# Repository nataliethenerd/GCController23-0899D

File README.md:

# Game Cube Controller 23-0899D reverse engineer

**ORDER WITH ENIG**

Thanks to the people who have supported me on Ko-Fi, you've made this possible! 

You can support me on Ko-Fi

## Scans

HD scans of the original board can be found [here](https://github.com/nataliethenerd/boardscans/tree/main/GCC-23-0899D)

**My socials**

• [Twitter](https://twitter.com/natalie_thenerd) 

• [Instagram](https://www.instagram.com/natalie.thenerd/) 

• [Modded Gameboy Club](https://moddedgameboy.club/) - a club dedicated to the modification of Game Boys, freely sharing resources

## License

Please do not remove my logo, website and name.

The CC BY-SA 4.0 (Creative Commons Attribution-ShareAlike 4.0 International) license allows you to:

1. **Share** - Copy and redistribute the material in any medium or format.
2. **Adapt** - Remix, transform, and build upon the material for any purpose, even commercially.

### Conditions:

- **Attribution** - You must give appropriate credit, provide a link to the license, and indicate if changes were made. You may do so in any reasonable manner, but not in any way that suggests the licensor endorses you or your use.
- **ShareAlike** - If you remix, transform, or build upon the material, you must distribute your contributions under the same license as the original.

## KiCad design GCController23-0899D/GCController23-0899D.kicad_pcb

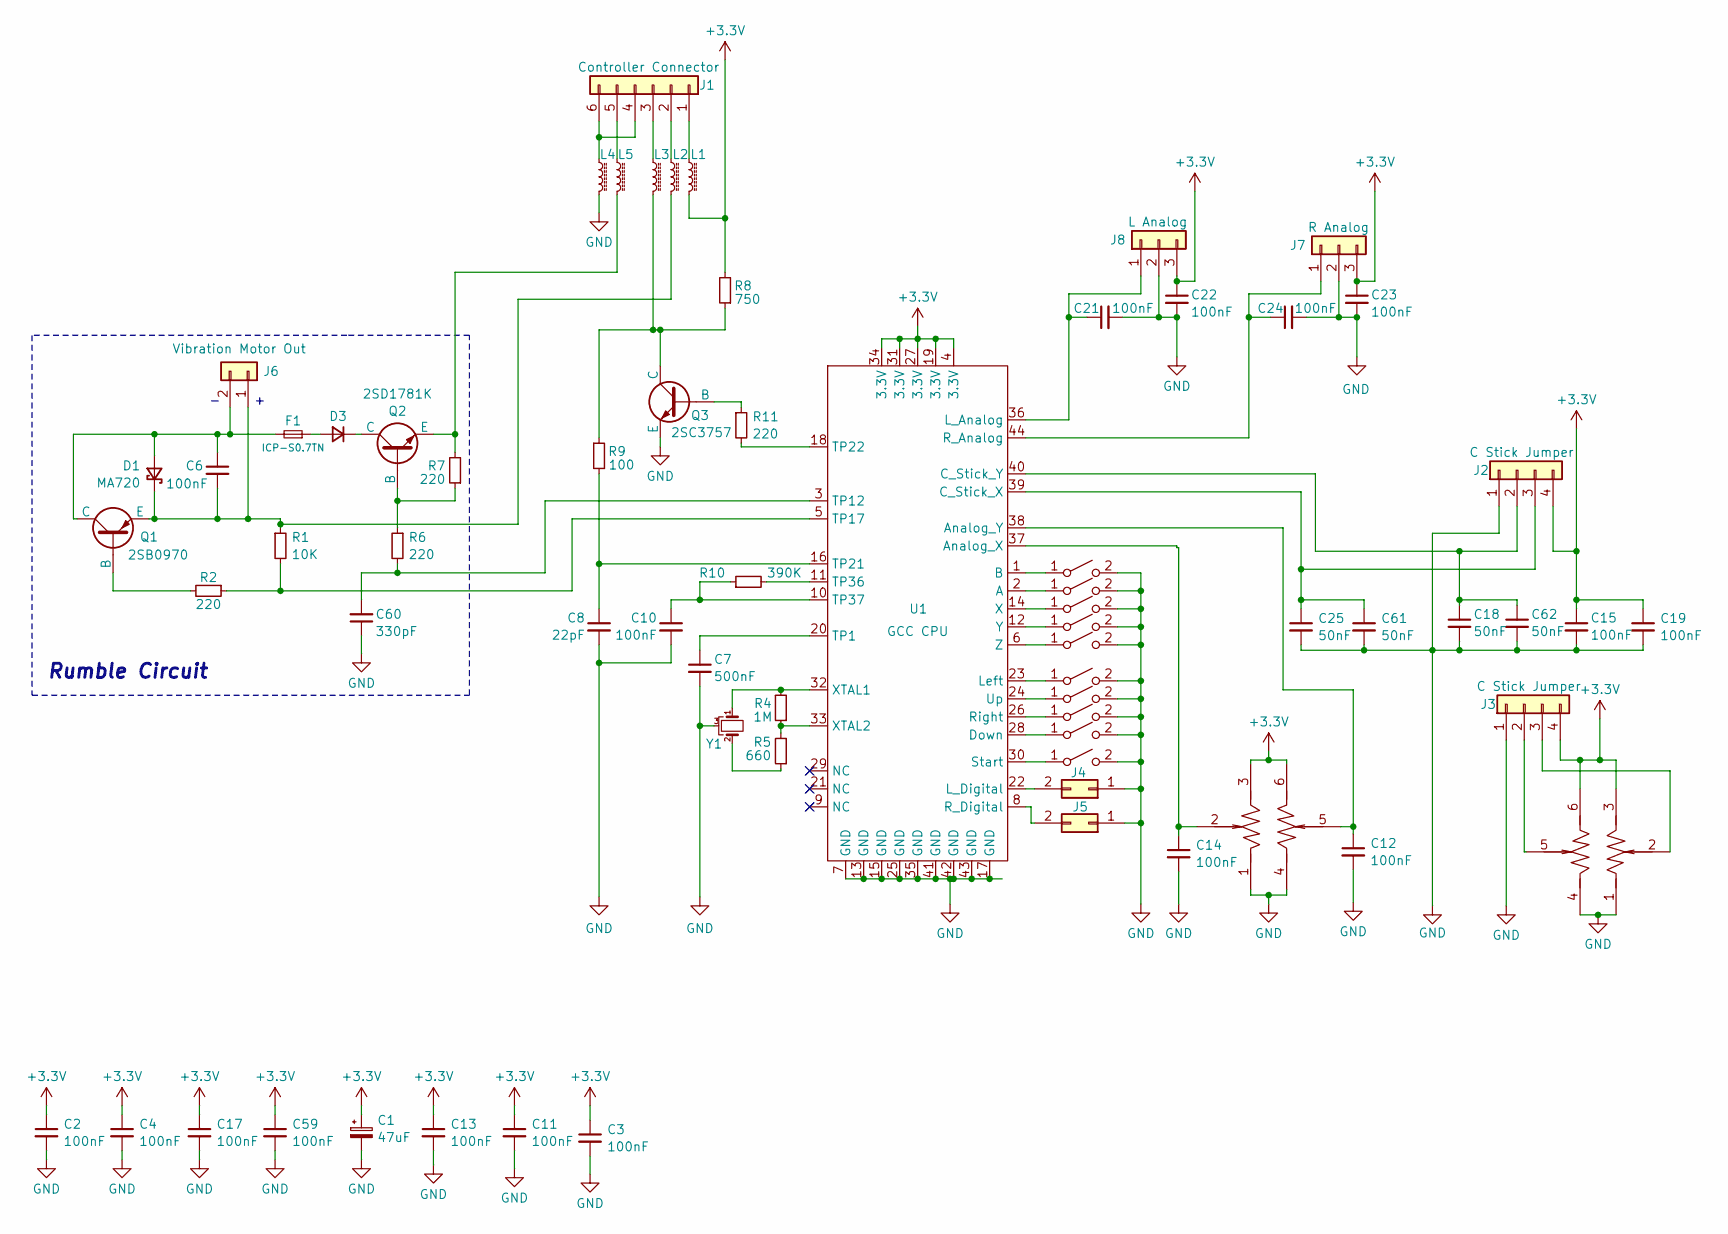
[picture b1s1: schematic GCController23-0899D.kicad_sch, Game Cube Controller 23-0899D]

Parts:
C1: 47uF; GCC_cap
C2, C3, C4, C6, C10, C11, C12, C13, C14, C15, C17, C19, C21, C22, C23, C24, C59: 100nF; C_0603_1608Metric
C7: 500nF; C_0603_1608Metric
C8: 22pF; C_0603_1608Metric
C18, C25, C61, C62: 50nF; C_0603_1608Metric
C60: 330pF; C_0603_1608Metric
D1: MA720; SOT-23
D3: D_Small; D_SOD-323_HandSoldering
F1: ICP-S0.7TN; Fuse_1210_3225Metric
J1: Controller Connector; PinSocket_1x06_P2.00mm_Vertical
J2, J3: C Stick Jumper; PinHeader_1x04_P2.00mm_Vertical
J4: L; GCC_DPad
J5: R; GCC_DPad
J6: Vibration Motor Out; SolderJumper-2_P1.3mm_Open_RoundedPad1.0x1.5mm
J7: R Analog; PinHeader_1x03_P2.54mm_Vertical
J8: L Analog; PinHeader_1x03_P2.54mm_Vertical
L1, L2, L4, L5: FerriteBead_Small; R_0805_2012Metric
L3: FerriteBead_Small; R_0603_1608Metric
Q1: 2SB0970; SOT-23
Q2: 2SD1781K; SOT-23
Q3: 2SC3757; SOT-323_SC-70
R1: 10K; R_0603_1608Metric
R2, R6, R7, R11: 220; R_0603_1608Metric
R4: 1M; R_0603_1608Metric
R5: 660; R_0603_1608Metric
R8: 750; R_0603_1608Metric
R9: 100; R_0603_1608Metric
R10: 390K; R_0603_1608Metric
SW1, SW2, SW7, SW8: SW_SPST; GCC_DPad
SW3, SW4, SW5, SW6: SW_SPST; GCC_ABXY
SW9: SW_SPST; GCC_Start
SW10: 3D161; GCC_CStick; LCSC Part C92593
SW11: SW_SPST
SW13: 3D161; GCC_Joystick; LCSC Part C92593
U1: GCC CPU; GCC_CPU
Y1: Crystal_GND3_Small; Resonator_SMD_Murata_CSTxExxV-3Pin_3.0x1.1mm

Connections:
+3.3V: C1.1, C2.1, C3.1, C4.1, C11.1, C13.1, C15.1, C17.1, C19.1, C22.1, C23.1, C59.1, J2.4, J3.4, J7.3, J8.3, L1.1, R8.2, SW10.3, SW10.6, SW13.3, SW13.6, U1.4 (3.3V), U1.19 (3.3V), U1.27 (3.3V), U1.31 (3.3V), U1.34 (3.3V)
GND: C1.2, C2.2, C3.2, C4.2, C7.2, C8.2, C10.2, C11.2, C12.2, C13.2, C14.2, C15.2, C17.2, C18.2, C19.2, C21.2, C22.2, C23.2, C24.2, C25.2, C59.2, C60.1, C61.2, C62.2, J2.1, J3.1, J4.1, J5.1, J7.2, J8.2, L4.2, Q3.2 (E), SW1.2 (B), SW2.2 (B), SW3.2 (B), SW4.2 (B), SW5.2 (B), SW6.2 (B), SW7.2 (B), SW8.2 (B), SW9.2 (B), SW10.1, SW10.4, SW11.2 (B), SW13.1, SW13.4, U1.7 (GND), U1.13 (GND), U1.15 (GND), U1.17 (GND), U1.25 (GND), U1.35 (GND), U1.41 (GND), U1.42 (GND), U1.43 (GND), Y1.3; also elsewhere on the board
unnamed: C6.1, D1.1 (A), F1.2, J6.2, Q1.3 (C)
unnamed: C6.2, D1.3 (K), J6.1, L2.2, Q1.2 (E), R1.1
unnamed: D3.2 (A), F1.1
unnamed: D3.1 (K), Q2.3 (C)
unnamed: J1.1, L1.2
unnamed: J1.2, L2.1
unnamed: J1.3, L3.1
unnamed: J1.4, J1.6, L4.1
unnamed: J1.5, L5.2
unnamed: C18.1, C62.1, J2.2, U1.40 (C_Stick_Y)
unnamed: C25.1, C61.1, J2.3, U1.39 (C_Stick_X)
unnamed: J3.2, SW10.5
unnamed: J3.3, SW10.2
unnamed 15: J4.2, U1.22 (L_Digital); also elsewhere on the board
unnamed 16: J5.2, U1.8 (R_Digital); also elsewhere on the board
unnamed: C24.1, J7.1, U1.44 (R_Analog)
unnamed: C21.1, J8.1, U1.36 (L_Analog)
unnamed: Q1.1 (B), R2.2
unnamed: Q2.2 (B), R6.1, R7.1
unnamed: L5.1, Q2.1 (E), R7.2
unnamed: Q3.1 (B), R11.1
unnamed: L3.2, Q3.3 (C), R8.1, R9.1
unnamed: R5.1, Y1.2
unnamed: SW1.1 (A), U1.24 (Up)
unnamed: SW2.1 (A), U1.23 (Left)
unnamed: SW3.1 (A), U1.14 (X)
unnamed: SW4.1 (A), U1.12 (Y)
unnamed: SW5.1 (A), U1.1 (B)
unnamed: SW6.1 (A), U1.2 (A)
unnamed: SW7.1 (A), U1.26 (Right)
unnamed: SW8.1 (A), U1.28 (Down)
unnamed: SW9.1 (A), U1.30 (Start)
unnamed: SW11.1 (A), U1.6 (Z)
unnamed: C14.1, SW13.2, U1.37 (Analog_X)
unnamed: C12.1, SW13.5, U1.38 (Analog_Y)
unnamed: C7.1, U1.20 (TP1)
unnamed: C60.2, R6.2, U1.3 (TP12)
unnamed: R1.2, R2.1, U1.5 (TP17)
unnamed: C8.1, R9.2, U1.16 (TP21)
unnamed: R11.2, U1.18 (TP22)
unnamed: R10.2, U1.11 (TP36)
unnamed: C10.1, R10.1, U1.10 (TP37)
unnamed: R4.2, U1.32 (XTAL1), Y1.1
unnamed: R4.1, R5.2, U1.33 (XTAL2)

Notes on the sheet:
Rumble Circuit

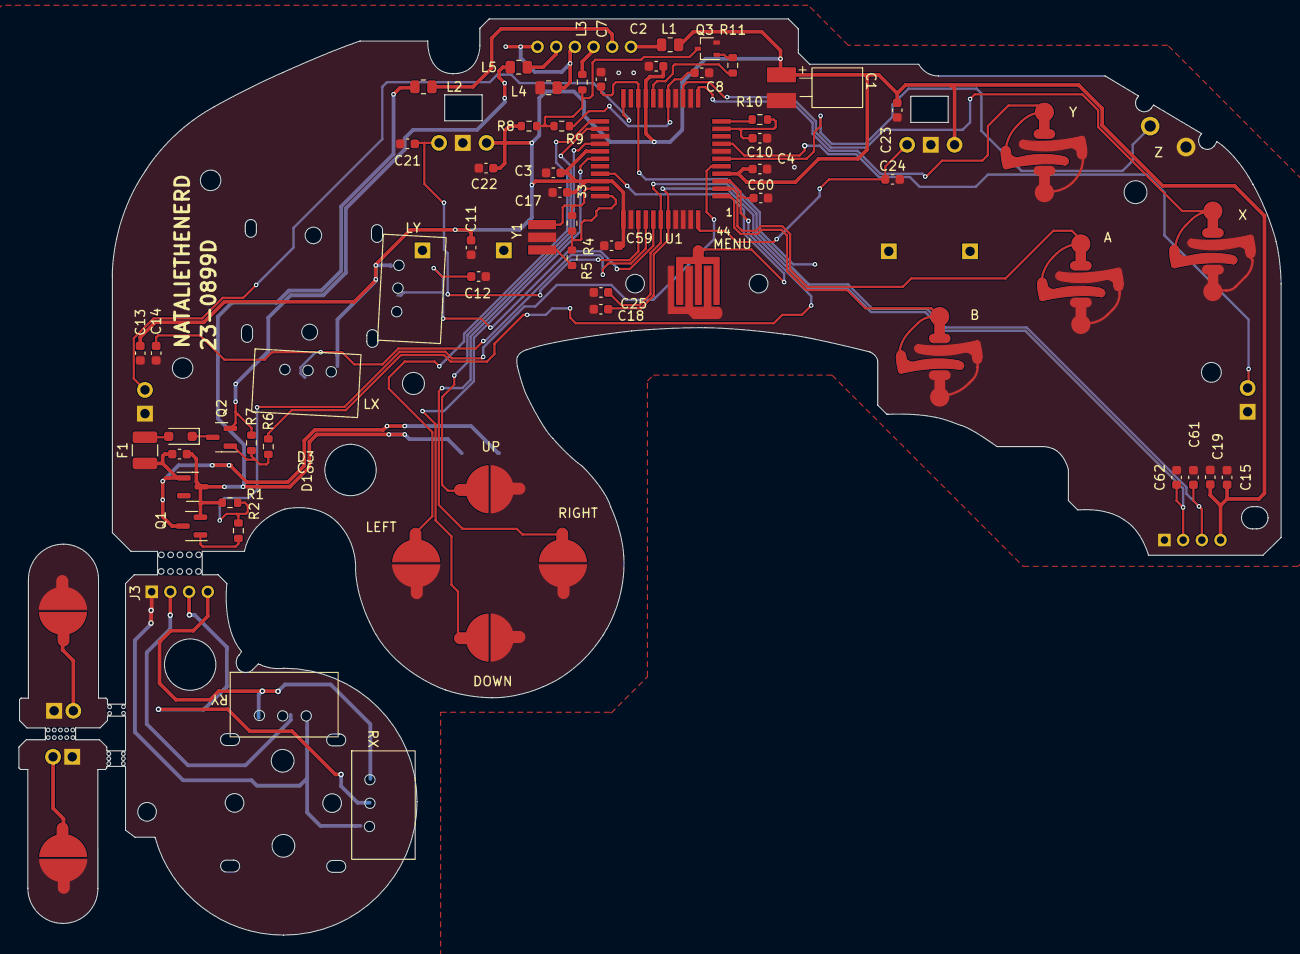
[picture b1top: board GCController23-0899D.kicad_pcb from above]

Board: 4 copper layers, 135.1 x 98.0 mm, 68 parts (0 on the bottom side), 45 nets.

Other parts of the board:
SW10#2, SW12: SW_SPST; PinHeader_1x02_P2.54mm_Vertical

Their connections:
GND: SW10#2.2 (B), SW12.2 (B); also elsewhere on the board
unnamed 15: SW10#2.1 (A); also elsewhere on the board
unnamed 16: SW12.1 (A); also elsewhere on the board

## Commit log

2024-07-15 kicad files
2024-07-15 added open source logo :smile:
2024-09-16 pdf schematics
